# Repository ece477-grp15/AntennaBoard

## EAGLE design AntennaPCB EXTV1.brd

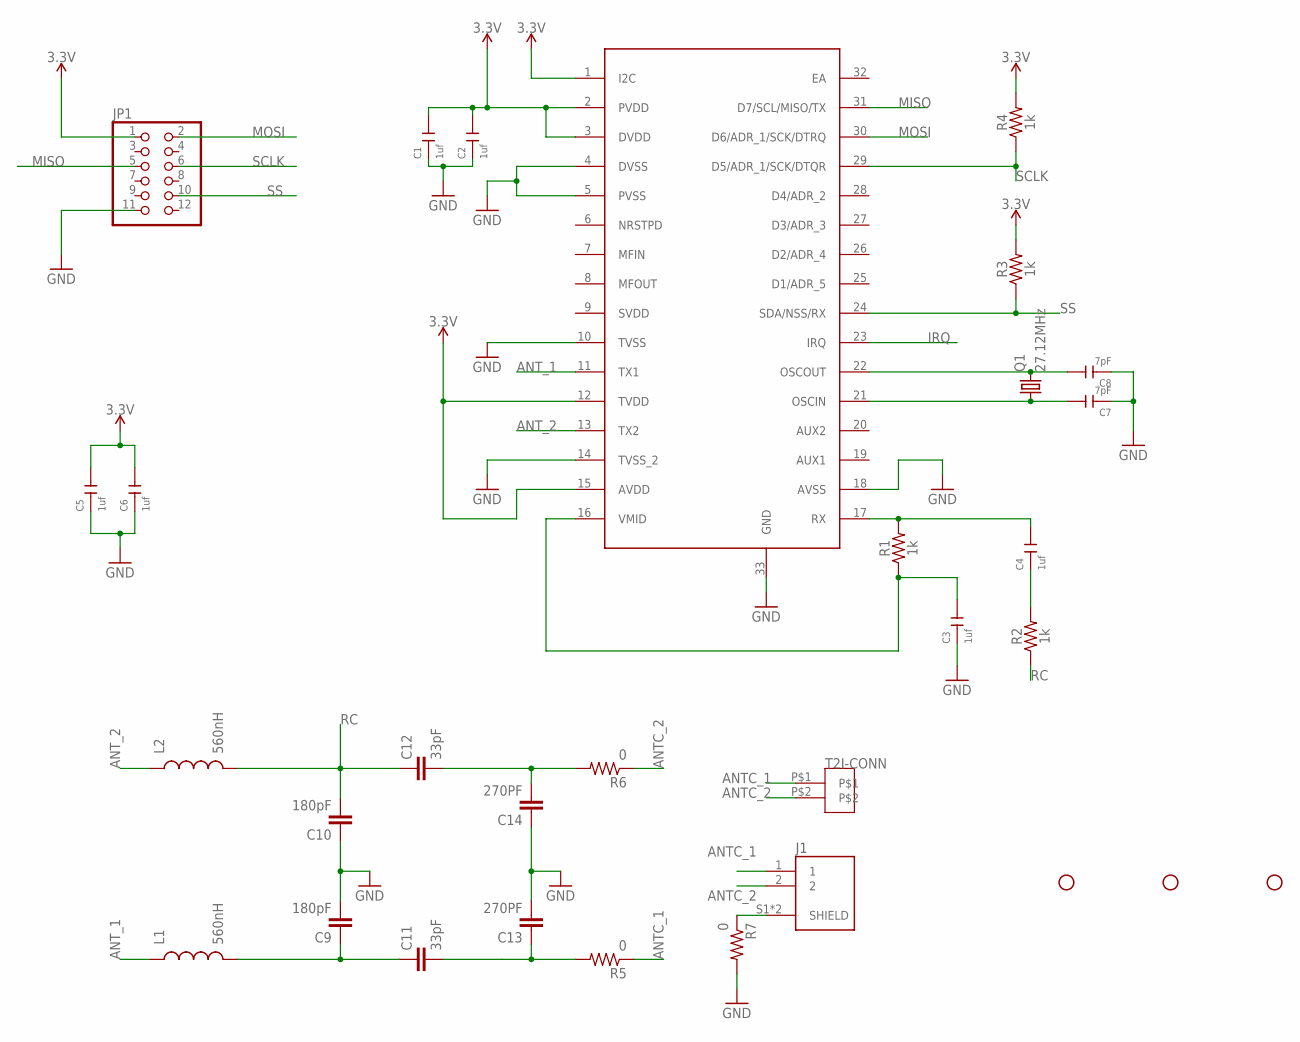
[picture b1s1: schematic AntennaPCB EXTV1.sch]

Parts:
C1, C2, C3, C4, C5, C6: 1uf; C0603
C7, C8: 7pF; C0603
C9, C10: 180pF; 0603
C11, C12: 33pF; 0603
C13, C14: 270PF; 0603
H1, H2, H3: STAND-OFF
J1: BM02B-ACHSS-GAN-TF(LF)(SN); JST_BM02B-ACHSS-GAN-TF(LF)(SN)
JP1: PINHD-2X6; 2X06
L1, L2: 560nH; L0603
Q1: 27.12MHz; HC49/S
R1, R2, R3, R4: 1k; 0603
R5, R6, R7: 0; RES_1206
U$1: MFRC522; HVQFN32
U$2: T2I-02

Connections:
3.3V: C1.2, C2.2, C5.2, C6.2, JP1.1, R3.2, R4.2, U$1.1 (I2C), U$1.2 (PVDD), U$1.3 (DVDD), U$1.12 (TVDD), U$1.15 (AVDD)
ANTC_1: J1.1, R5.1, U$2.P$1
ANTC_2: J1.2, R6.1, U$2.P$2
ANT_1: L1.1, U$1.11 (TX1)
ANT_2: L2.1, U$1.13 (TX2)
GND: C1.1, C2.1, C3.1, C5.1, C6.1, C7.1, C8.1, C9.2, C10.1, C13.2, C14.1, JP1.11, R7.2, U$1.4 (DVSS), U$1.5 (PVSS), U$1.10 (TVSS), U$1.14 (TVSS_2), U$1.18 (AVSS), U$1.33 (GND)
IRQ: U$1.23 (IRQ)
MISO: JP1.5, U$1.31 (D7/SCL/MISO/TX)
MOSI: JP1.2, U$1.30 (D6/ADR_1/SCK/DTRQ)
unnamed: C3.2, R1.1, U$1.16 (VMID)
unnamed: C4.2, R1.2, U$1.17 (RX)
unnamed: C4.1, R2.2
unnamed: C8.2, Q1.2, U$1.22 (OSCOUT)
unnamed: C7.2, Q1.1, U$1.21 (OSCIN)
unnamed: J1.S1 (SHIELD), J1.S2 (SHIELD), R7.1
unnamed: C9.1, C11.1, L1.2
unnamed: C11.2, C13.1, R5.2
unnamed: C12.2, C14.2, R6.2
RC: C10.2, C12.1, L2.2, R2.1
SCLK: JP1.6, R4.1, U$1.29 (D5/ADR_1/SCK/DTQR)
SS: JP1.10, R3.1, U$1.24 (SDA/NSS/RX)

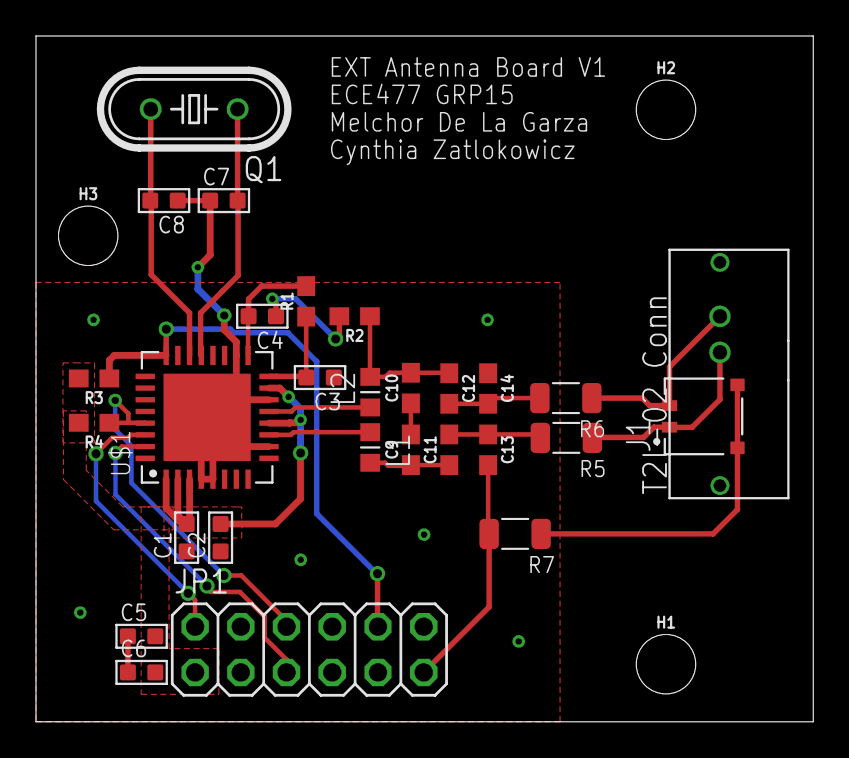
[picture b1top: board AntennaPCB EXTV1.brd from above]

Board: 2 copper layers, 43.2 x 38.1 mm, 31 parts (0 on the bottom side), 20 nets.

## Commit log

2020-02-11 added schematic
2020-02-26 addded part
2020-02-26 updated schematic with RFID reader
2020-03-03 Created the schematic for external Antenna circuit
2020-03-04 Added connectors for the ACH Antenna
2020-03-04 Created the layout for routing the External antenna board
2020-03-04 Repositioning components on board
2020-03-05 Re-created some parts on a schematic and did some more positioning adjustments as well as DRC
2020-03-05 Copied the Antenna board from external circuit to create my own antenna.
2020-03-05 Created the antenna board and adjusted sizing of the board
2020-03-06 Moved more stuff around and edited via sizes
2020-03-06 Put stand-offs on the board
2020-03-06 moved Standoffs
2020-03-14 Antenna redesign

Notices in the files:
parts and their libraries:
SparkFun-Capacitors: Licensing: Creative Commons ShareAlike 4.0 International - https://creativecommons.org/licenses/by-sa/4.0
